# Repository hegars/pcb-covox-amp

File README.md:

# Modded verison of pcb-covox-amp

slimed down version of [forked](https://github.com/yeokm1/pcb-covox-amp)

## Changelog

* Added pads of inline DB25
* Ordered Resistor Ladder
* Added output selector so you dont have to populate amp abd use only one 3.5mm connector
* Using RK097N potentiometers 

# pcb-covox-amp
A tiny sound card based on the Covox Speech Thing design which includes an LM386 amplifier. I have another design that just has the resistor ladder portion only without the amplifier which can be found [here](https://github.com/yeokm1/pcb-covox).

##PCB Design software and addons used

1. Kicad 4.0.2 or later

##Video

Due to copyright problems in the music used, this video can only be viewed on a PC. It is blocked on mobile devices and other platforms.

##Images

The picture is of the Rev 2 version with the bug in the limited parallel port grounding. This has been corrected in the Rev 3 gerber but not fabricated.

##Schematic drawings

##Parts required
Use Libreoffice to open [pcb-covox-amp-bom.ods](pcb-covox-amp-bom.ods)

##References
1. [Hardware implementation references](https://blog.frantovo.cz/c/307/DAC%20%28zvukov%C3%A1%20karta%29%20pro%20LPT%20port%20a.k.a.%20Covox)
2. [Design reference](http://kb.gr8bit.ru/KB0010/GR8BIT-KB0010-Adding-multimedia-capability-covox-device.html)
3. [MJ-2135 package referenced from coqui-dip](https://github.com/open-eie/coqui-dip)
4. [Amplifier circuit](http://www.circuitbasics.com/build-a-great-sounding-audio-amplifier-with-bass-boost-from-the-lm386/)

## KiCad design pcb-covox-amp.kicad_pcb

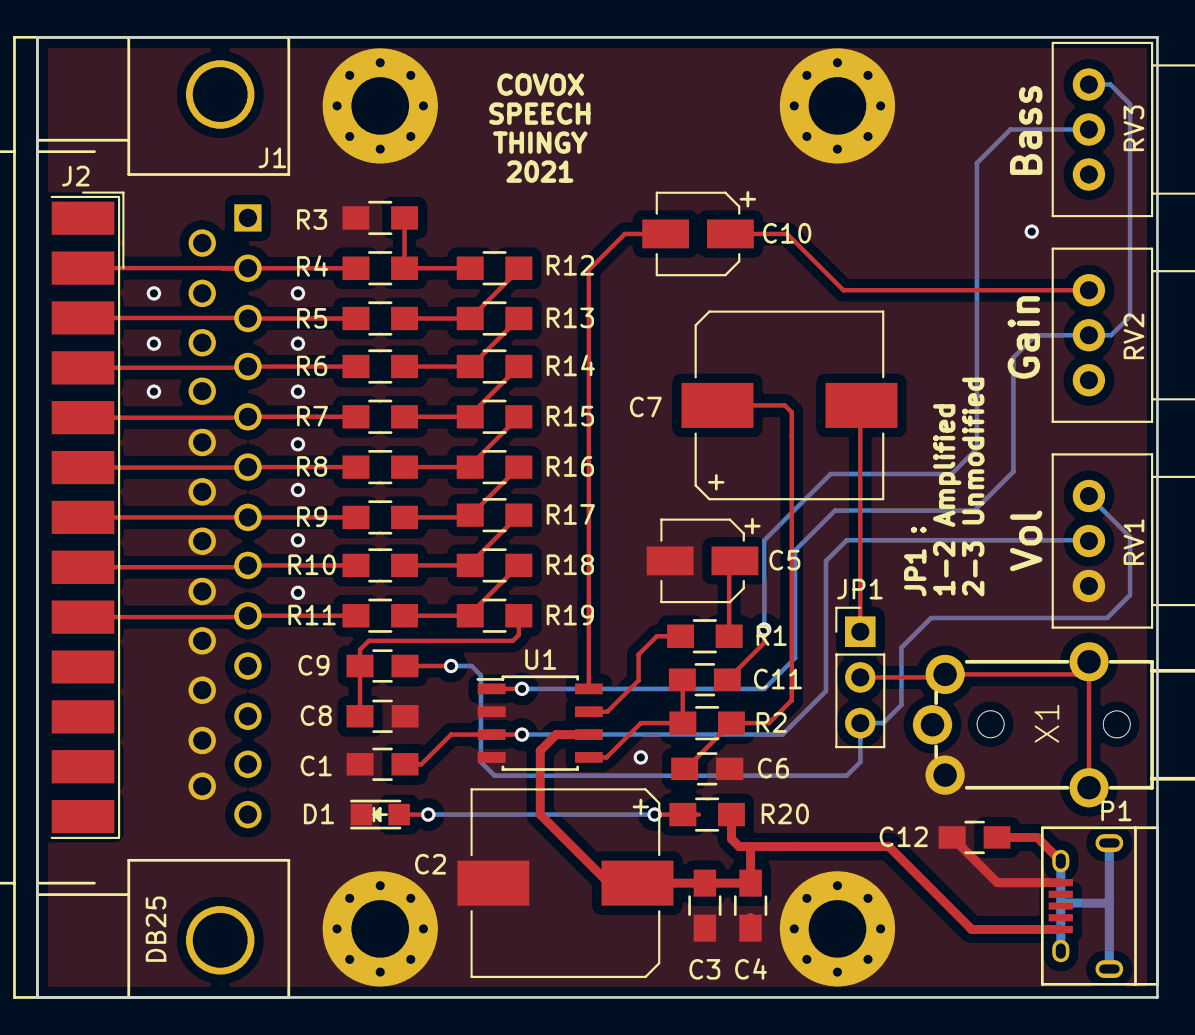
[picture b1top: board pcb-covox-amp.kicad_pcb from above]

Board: 2 copper layers, 62.2 x 53.3 mm, 46 parts (0 on the bottom side), 33 nets.

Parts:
C1: 470pF; C_0805_HandSoldering
C2: 100uF; CP_Elec_10x10.5
C3, C4, C6, C9, C12: 0.1uF; C_0805_HandSoldering
C5, C10: 10uF; CP_Elec_4x5.3
C7: 1000uF; CP_Elec_10x10.5
C8: 0.01uF; C_0805_HandSoldering
C11: 33000pF; C_0805_HandSoldering
D1: Yellow; LED_0805
J1: DB25; DB25MC
J2: DB25; DSUB-25_Male_EdgeMount_P2.77mm
JP1: Jumper_3_Open; Pin_Header_Straight_1x03_Pitch2.54mm
MH1, MH2, MH3, MH4: MOUNTHOLE; MountingHole_3.2mm_M3_Pad_Via
P1: USB; USB_Micro-B
R1, R12, R13, R14, R15, R16, R17, R18, R19: 10K; R_0805_HandSoldering
R2: 10; R_0805_HandSoldering
R3, R4, R5, R6, R7, R8, R9, R10, R11: 20K; R_0805_HandSoldering
R20: 1500; R_0805_HandSoldering
RV1, RV2, RV3: 10K; Potentiometer_Alps_RK09Y_Vertical
U1: LM386; SOIC-8_3.9x4.9mm_Pitch1.27mm
X1: Amp; mj-2135-MJ-2135

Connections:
+5V: C2.1, C3.1, C4.1, P1.1, R20.1, U1.6
Amp-Audio: C7.2, JP1.1
Data0: J1.2, J2.2, R4.2
Data1: J1.3, J2.3, R5.2
Data2: J1.4, J2.4, R6.2
Data3: J1.5, J2.5, R7.2
Data4: J1.6, J2.6, R8.2
Data5: J1.7, J2.7, R9.2
Data6: J1.8, J2.8, R10.2
Data7: J1.9, J2.9, R11.2
GND: C1.1, C2.2, C3.2, C4.2, C5.2, C6.2, C8.2, C12.1, D1.1, J1.18, J1.19, J1.20, J1.21, J1.22, J1.23, J1.24, J1.25, J2.18, J2.19, J2.20, J2.21, J2.22, J2.23, J2.24, J2.25, MH1.1, MH2.1, MH3.1, MH4.1, P1.5, R3.2, RV1.1, U1.2, U1.4, X1.P$2
Gain1: RV2.2, RV3.3, U1.1
Gain8: C10.2, U1.8
Input+: C1.2, RV1.2, U1.3
unnamed: C5.1, R1.1
unnamed: C6.1, C7.1, R2.1
unnamed: C8.1, C9.1, R19.1
unnamed: C10.1, RV2.3
unnamed: C11.2, RV3.2
unnamed: C12.2, P1.6
unnamed: D1.2, R20.2
unnamed: JP1.2, X1.P$3, X1.P$4, X1.P$5
unnamed: R1.2, U1.7
unnamed: R10.1, R17.1, R18.2
unnamed: R11.1, R18.1, R19.2
unnamed: R5.1, R12.1, R13.2
unnamed: R3.1, R4.1, R12.2
unnamed: R6.1, R13.1, R14.2
unnamed: R7.1, R14.1, R15.2
unnamed: R8.1, R15.1, R16.2
unnamed: R9.1, R16.1, R17.2
Source-Audio: C9.2, JP1.3, RV1.3
Vout: C11.1, R2.2, U1.5

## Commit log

2021-02-27 updated modded version
